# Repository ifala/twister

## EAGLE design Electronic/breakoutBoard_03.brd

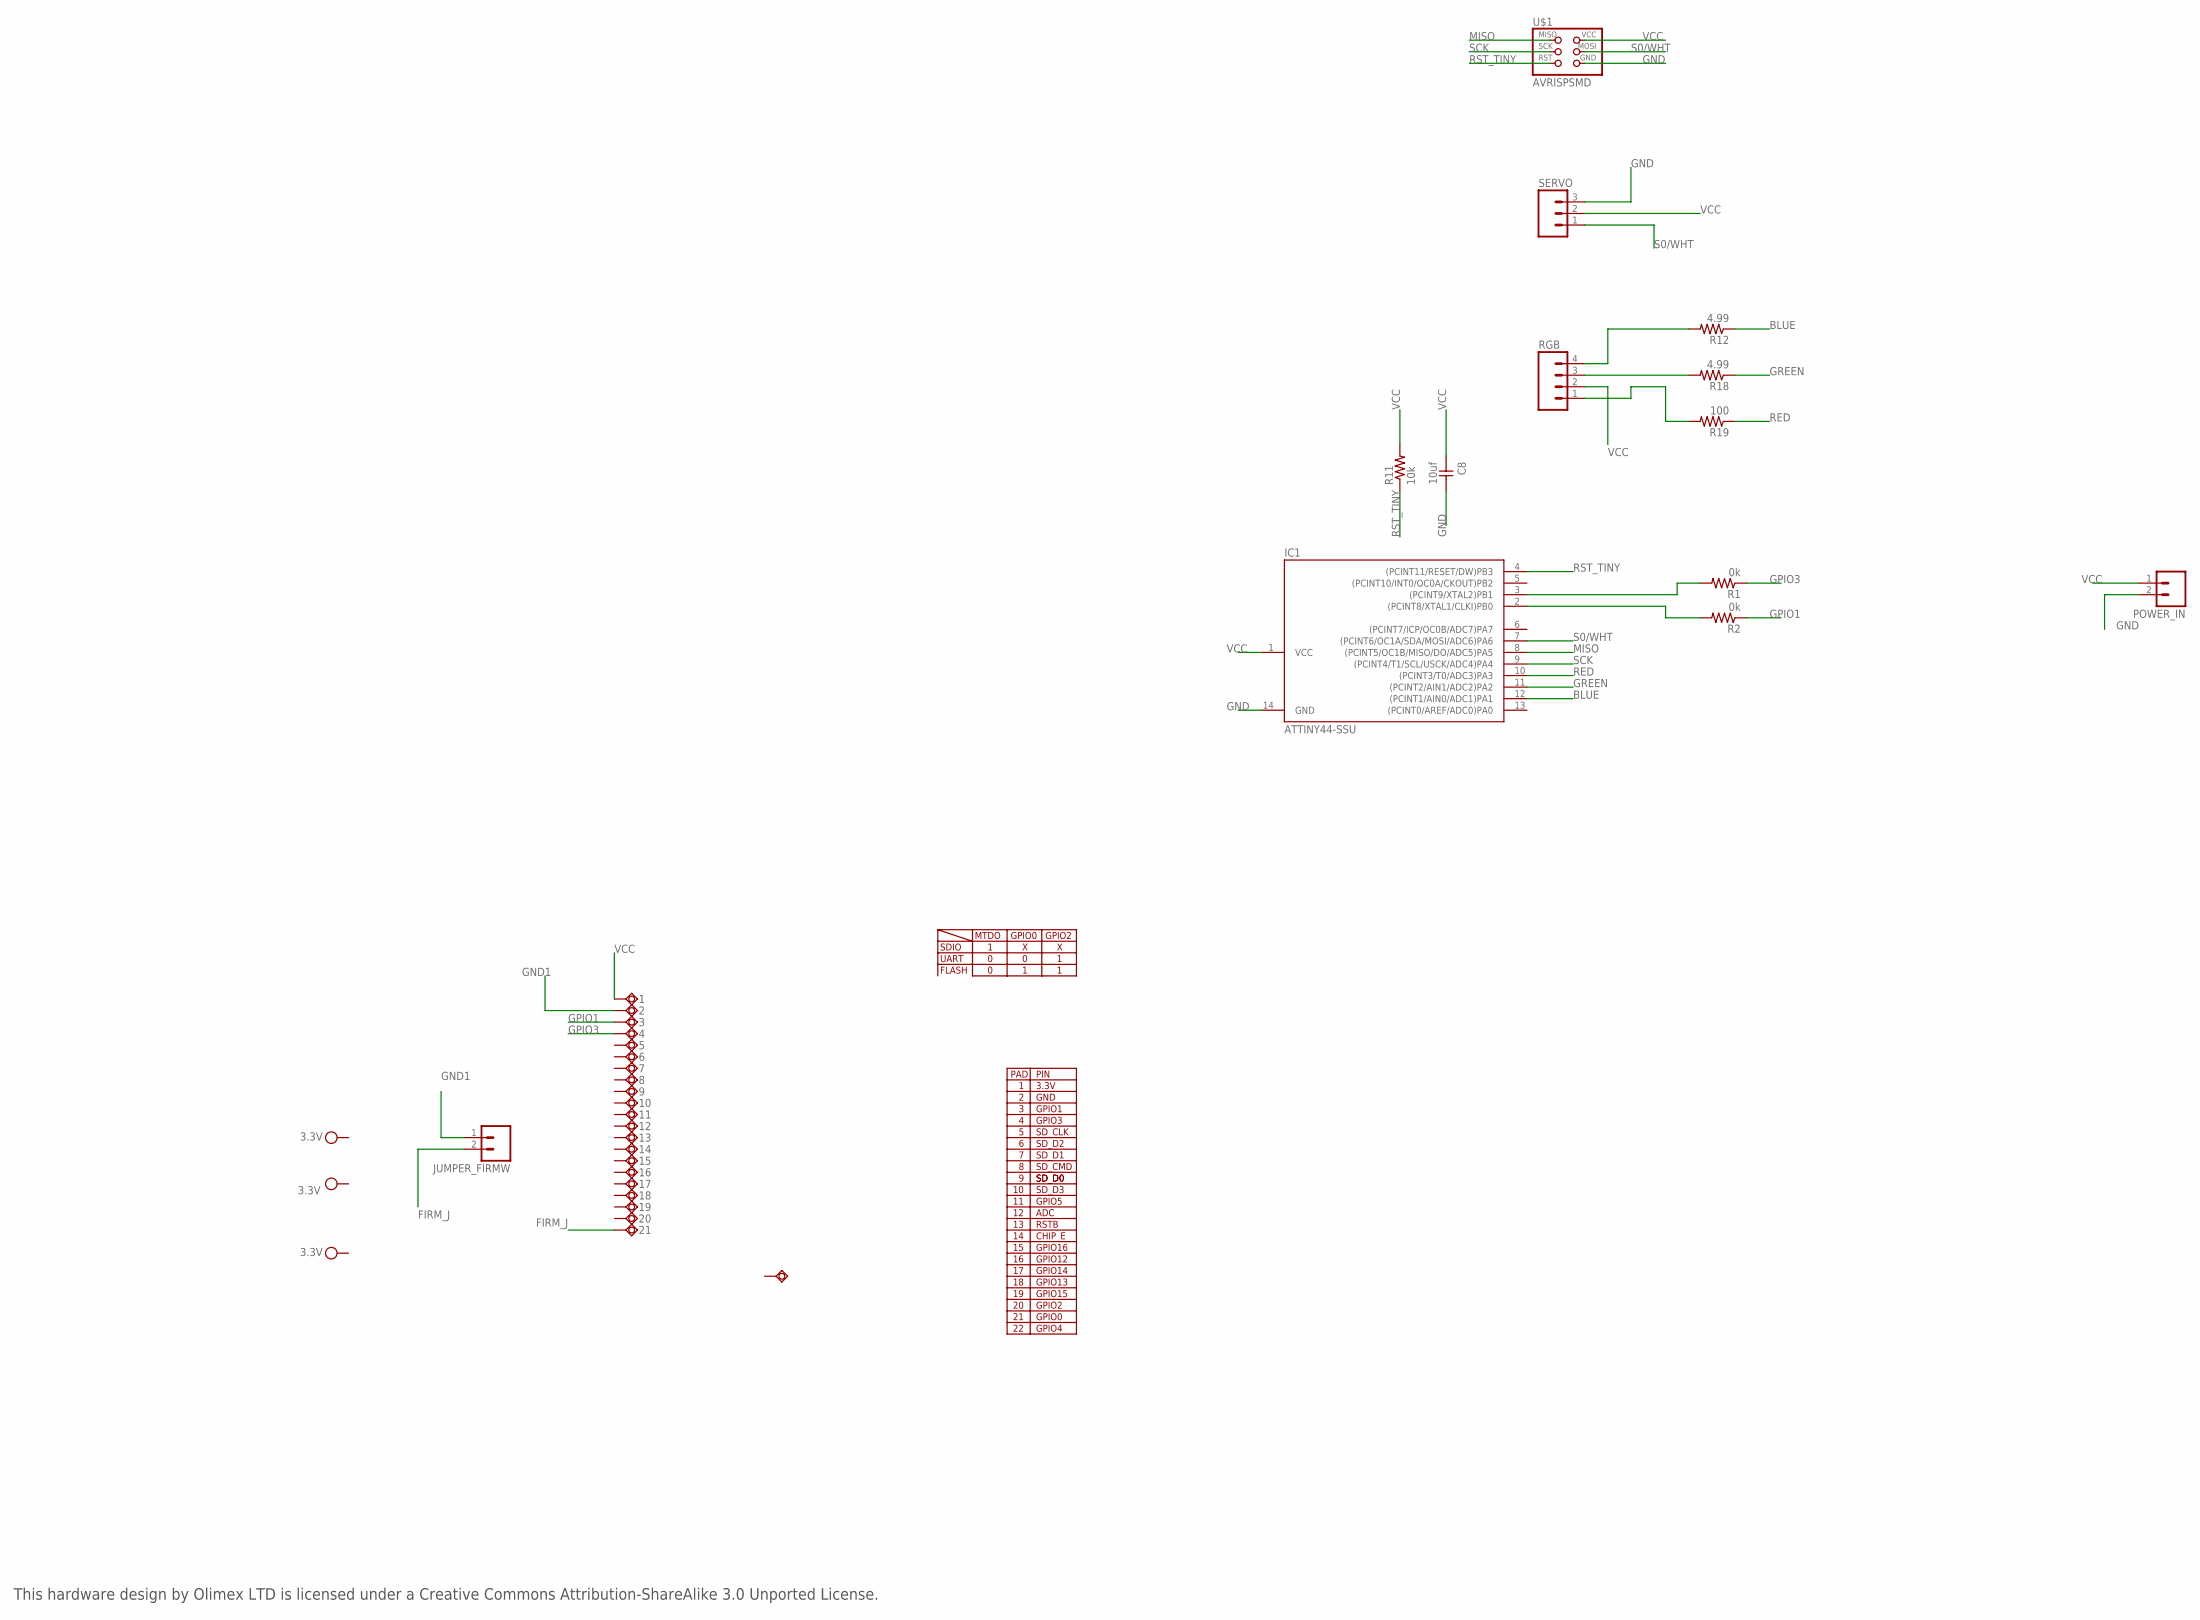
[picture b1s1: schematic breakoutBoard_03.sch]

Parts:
1, 2, 3, 4, 5, 6, 7, 8, 9, 10, 11, 12, 13, 14, 15, 16, 17, 18, 19, 20, 21, 22: TESTPAD8; TESTPAD50/80
C8: 10uf; 1206
IC1: ATTINY44-SSU; SOIC14
JUMPER_FIRMW: M02LOCK_LONGPADS; 1X02_LOCK_LONGPADS
POWER_IN: M02LOCK_LONGPADS; 1X02_LOCK_LONGPADS
R1, R2: 0k; 1206
R11: 10k; 1206
R12, R18: 4.99; 1206
R19: 100; 1206
RGB: M04LONGPADS; 1X04_LONGPADS
SERVO: M03LOCK_LONGPADS; 1X03_LOCK_LONGPADS
U$1: AVRISPSMD; 2X03SMD

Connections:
BLUE: IC1.12 ((PCINT1/AIN0/ADC1)PA1), R12.1
FIRM_J: 21.P$1, JUMPER_FIRMW.2
GND: C8.2, IC1.14 (GND), POWER_IN.2, SERVO.3, U$1.6 (GND)
GND1: 2.P$1, JUMPER_FIRMW.1
GPIO1: 3.P$1, R2.1
GPIO3: 4.P$1, R1.1
GREEN: IC1.11 ((PCINT2/AIN1/ADC2)PA2), R18.1
MISO: IC1.8 ((PCINT5/OC1B/MISO/DO/ADC5)PA5), U$1.1 (MISO)
unnamed: IC1.3 ((PCINT9/XTAL2)PB1), R1.2
unnamed: IC1.2 ((PCINT8/XTAL1/CLKI)PB0), R2.2
unnamed: R12.2, RGB.4
unnamed: R18.2, RGB.3
unnamed: R19.2, RGB.1
RED: IC1.10 ((PCINT3/T0/ADC3)PA3), R19.1
RST_TINY: IC1.4 ((PCINT11/RESET/DW)PB3), R11.1, U$1.5 (RST)
S0/WHT: IC1.7 ((PCINT6/OC1A/SDA/MOSI/ADC6)PA6), SERVO.1, U$1.4 (MOSI)
SCK: IC1.9 ((PCINT4/T1/SCL/USCK/ADC4)PA4), U$1.3 (SCK)
VCC: 1.P$1, C8.1, IC1.1 (VCC), POWER_IN.1, R11.2, RGB.2, SERVO.2, U$1.2 (VCC)

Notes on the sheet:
SDIO
UART
FLASH
MTDO
GPIO0
GPIO2
PAD
GPIO1
GPIO3
SD_CLK
SD_D0
SD_D1
SD_D2
SD_D3
SD_CMD
3.3V
GND
GPIO5
GPIO4
GPIO15
GPIO13
GPIO12
GPIO14
GPIO16
ADC
PIN
RSTB
CHIP_E
This hardware design by Olimex LTD is licensed under a Creative Commons Attribution-ShareAlike 3.0 Unported License.

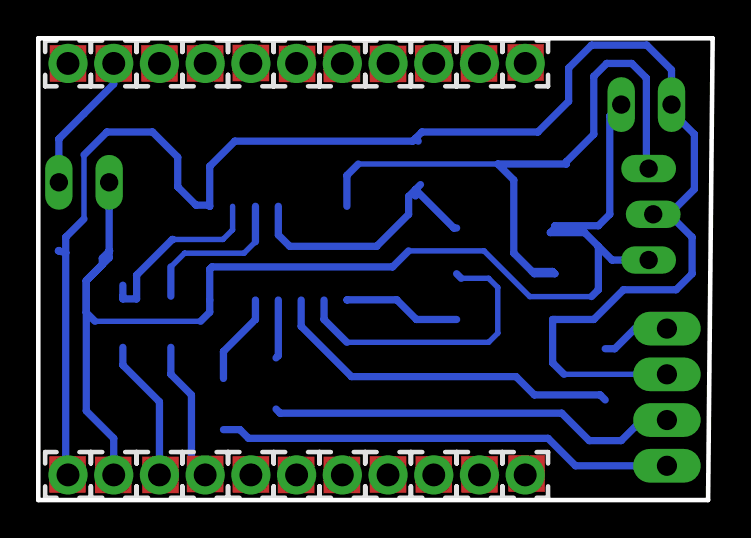
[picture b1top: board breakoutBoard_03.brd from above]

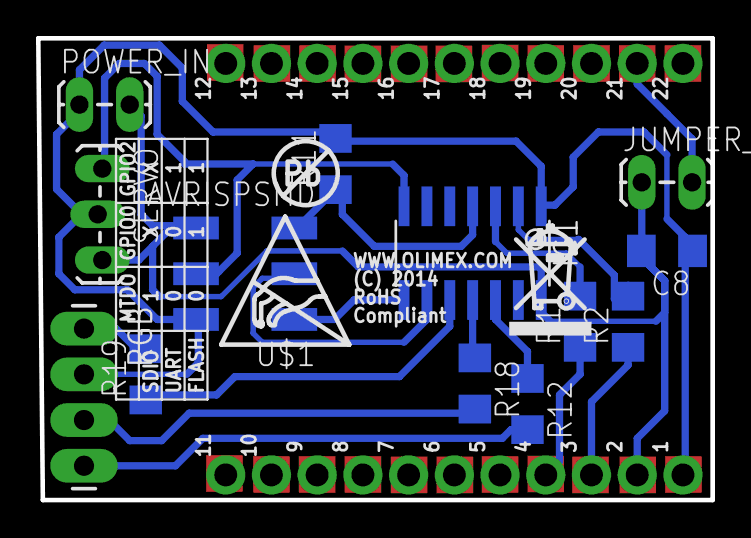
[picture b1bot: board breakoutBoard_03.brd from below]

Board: 2 copper layers, 37.5 x 25.7 mm, 38 parts (16 on the bottom side), 18 nets.

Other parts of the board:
U$4: ESD_SYMBOL
U$6: PB_SMALL
U$7: RECYCLE_BIN1/8

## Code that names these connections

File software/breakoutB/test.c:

//
//
// hello.ftdi.44.echo.c
//
// 115200 baud FTDI character echo, with flash string
//
// set lfuse to 0x7E for 20 MHz xtal
//
// Neil Gershenfeld
// 12/8/10
//
// (c) Massachusetts Institute of Technology 2010
// Permission granted for experimental and personal use;
// license for commercial sale available from MIT.
//

#include <stdlib.h>
#include <avr/io.h>
#include <util/delay.h>
#include <avr/pgmspace.h>
#include <avr/interrupt.h>

#define output(directions,pin) (directions |= pin) // set port direction for output
#define set(port,pin) (port |= pin) // set port pin
#define clear(port,pin) (port &= (~pin)) // clear port pin
#define pin_test(pins,pin) (pins & pin) // test for port pin
#define bit_test(byte,bit) (byte & (1 << bit)) // test for bit set
#define bit_delay_time 100 // bit delay for 115200 with overhead
#define bit_delay() _delay_us(bit_delay_time) // RS232 bit delay
#define half_bit_delay() _delay_us(bit_delay_time/2) // RS232 half bit delay
#define char_delay() _delay_ms(10) // char delay
#define position_delay() _delay_ms(500)
#define PWM_delay() _delay_us(25) // PWM delay

#define serial_port PORTB
#define serial_direction DDRB
#define serial_pins PINB
#define serial_pin_in (1 << PB0)
#define serial_pin_out (1 << PB1)


#define servo_port PORTA
#define servo_direction DDRA
#define servo_pin (1<<PA6)

#define red_led_port PORTA
#define red_led_direction DDRA
#define red (1 << PA3)

#define green_led_port PORTA
#define green_led_direction DDRA
#define green (1 << PA2)

#define blue_led_port PORTA
#define blue_led_direction DDRA
#define blue (1 << PA1)

#define max_buffer 25

void get_char(volatile unsigned char *pins, unsigned char pin, char *rxbyte) {
   //
   // read character into rxbyte on pins pin
   //    assumes line driver (inverts bits)
   //
   *rxbyte = 0;
   while (pin_test(*pins,pin))
      //
      // wait for start bit
      //
      ;
   //
   // delay to middle of first data bit
   //
   half_bit_delay();
   bit_delay();
   //
   // unrolled loop to read data bits
   //
   if pin_test(*pins,pin)
      *rxbyte |= (1 << 0);
   else
      *rxbyte |= (0 << 0);
   bit_delay();
   if pin_test(*pins,pin)
      *rxbyte |= (1 << 1);
   else
      *rxbyte |= (0 << 1);
   bit_delay();
   if pin_test(*pins,pin)
      *rxbyte |= (1 << 2);
   else
      *rxbyte |= (0 << 2);
   bit_delay();
   if pin_test(*pins,pin)
      *rxbyte |= (1 << 3);
   else
      *rxbyte |= (0 << 3);
   bit_delay();
   if pin_test(*pins,pin)
      *rxbyte |= (1 << 4);
   else
      *rxbyte |= (0 << 4);
   bit_delay();
   if pin_test(*pins,pin)
      *rxbyte |= (1 << 5);
   else
      *rxbyte |= (0 << 5);
   bit_delay();
   if pin_test(*pins,pin)
      *rxbyte |= (1 << 6);
   else
      *rxbyte |= (0 << 6);
   bit_delay();
   if pin_test(*pins,pin)
      *rxbyte |= (1 << 7);
   else
      *rxbyte |= (0 << 7);
   //
   // wait for stop bit
   //
   bit_delay();
   half_bit_delay();
   }

void put_char(volatile unsigned char *port, unsigned char pin, char txchar) {
   //
   // send character in txchar on port pin
   //    assumes line driver (inverts bits)
   //
   // start bit
   //
   clear(*port,pin);
   bit_delay();
   //
   // unrolled loop to write data bits
   //
   if bit_test(txchar,0)
      set(*port,pin);
   else
      clear(*port,pin);
   bit_delay();
   if bit_test(txchar,1)
      set(*port,pin);
   else
      clear(*port,pin);
   bit_delay();
   if bit_test(txchar,2)
      set(*port,pin);
   else
      clear(*port,pin);
   bit_delay();
   if bit_test(txchar,3)
      set(*port,pin);
   else
      clear(*port,pin);
   bit_delay();
   if bit_test(txchar,4)
      set(*port,pin);
   else
      clear(*port,pin);
   bit_delay();
   if bit_test(txchar,5)
      set(*port,pin);
   else
      clear(*port,pin);
   bit_delay();
   if bit_test(txchar,6)
      set(*port,pin);
   else
      clear(*port,pin);
   bit_delay();
   if bit_test(txchar,7)
      set(*port,pin);
   else
      clear(*port,pin);
   bit_delay();
   //
   // stop bit
   //
   set(*port,pin);
   bit_delay();
   //
   // char delay
   //
   bit_delay();
   }

void put_string(volatile unsigned char *port, unsigned char pin, char *str) {
   //
   // print a null-terminated string
   //
   static int index;
   index = 0;
   do {
      put_char(port, pin, str[index]);
      ++index;
      } while (str[index] != 0);
   }
   

void accendiLed(int r, int g, int b){
	
	
	// /put_string(&serial_port, serial_pin_out, "Accendi led");
	
	if (r == 0) {
		set(red_led_port,red);
	} else {
 		clear(red_led_port,red);
	}
	if (g == 0) {
		set(green_led_port,green);
	} else {
		clear(green_led_port,green);
	}
	if (b == 0) {
		set(blue_led_port,blue);
	} else {
		clear(blue_led_port,blue);
	}
}

void muoviServo(int gradi){
	
	put_char(&serial_port, serial_pin_out, 'A');
	OCR1A = 500+(100*gradi);
	position_delay();
}
   
void doCommand(char cmd, char param){
	if (cmd == '0'){
		int p = atoi(&param);
		//led
		if (p==0) accendiLed(0,0,0);
		if (p==1) accendiLed(255,0,0);
		if (p==2) accendiLed(0,255,0);
		if (p==3) accendiLed(0,0,255);
		
	}
	if (cmd == '1'){
		int p = atoi(&param);
		muoviServo(p);
		// if (param == 0){
		// 	muoviServo(0);
		// } else {
		// 	muoviServo(1);
		// }
		
	}

}

int main(void) {
   //
   // main
   //
   static char chr;
   char* buffer;
   static int index;
   static char cmd;
   
      // initialize LED pins
   
   set(red_led_port, red);
   output(red_led_direction, red);
   set(green_led_port, green);
   output(green_led_direction, green);
   set(blue_led_port, blue);
   output(blue_led_direction, blue);
   //
   
   buffer = malloc(sizeof(char) * max_buffer);
   // set clock divider to /1
   //
   CLKPR = (1 << CLKPCE);
   CLKPR = (0 << CLKPS3) | (0 << CLKPS2) | (0 << CLKPS1) | (0 << CLKPS0);
   //
   // initialize output pins
   // set up timer 1
   //
   TCCR1A = (1 << COM1A1) | (0 << COM1A0); // clear OC1A on compare match
   TCCR1B = (0 << CS12) | (1 << CS11) | (0 << CS10) | (1 << WGM13); // prescaler /8, phase and frequency correct PWM, ICR1 TOP
   ICR1 = 20000; // 20 ms frequency
   sei();
   //
   //
   set(serial_port, serial_pin_out);
   output(serial_direction, serial_pin_out);
   
   clear(servo_port, servo_pin);
   output(servo_direction, servo_pin);
   //
   // main loop
   //
   index = 0;
   put_string(&serial_port, serial_pin_out, "Init.");
   while (1) {
      get_char(&serial_pins, serial_pin_in, &chr);
      if (chr=='\n'){
	      char t='t';
	      put_char(&serial_pins, serial_pin_out, t);
      }
      if (chr=='#') {
	      index=0;
	      get_char(&serial_pins, serial_pin_in, &chr);
              cmd = chr;
	      get_char(&serial_pins, serial_pin_in, &chr);
	      doCommand(cmd, chr);
      }
   }
}

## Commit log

2015-06-30 upload 1

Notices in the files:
Electronic/breakoutBoard_03.brd:
(C) 2014
parts and their libraries:
SparkFun-Connectors: Licensing: Creative Commons ShareAlike 4.0 International - https://creativecommons.org/licenses/by-sa/4.0
